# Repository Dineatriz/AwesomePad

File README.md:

# AwesomePad
---

## Overview

This macropad was made and designed to help gamers who frequently use Discord and people who do livestreams. With 6 customizable switches, a 2U switch with push-to-talk functionality, 3 configurable knobs, and an OLED panel, it can do almost anything the user wants.

---

## Schematic

---

## PCB

---

## Case

The case is 3D printed in 2 parts (Top + Bottom) and fits the PCB snugly with cutouts for all switches, the encoder, the OLED, knobs, and the USB-C port.

---

## BOM (Bill of Materials)

## Main Components
| Item           | Qtd. | Name                                                         | Link                        | Price(USD)  |
| -------------- | ---- | ------------------------------------------------------------ | --------------------------- | ----------- |
| Pro Micro      | 1    | **Pro Micro ATmega32U4 5V 16MHz USB-C 24 pin**               | https://amzn.eu/d/027iGPug  | $10.68      |
| OLED Display   | 1    | **OLED 0.96 inch SSD1306 I2C 4 pin**                         | https://amzn.eu/d/0ihcXsfb  | $9.49       |
| Rotary Encoder | 3    | **EC11 rotary encoder 20mm D shaft**                         | https://amzn.eu/d/0cy0BtVi  | $10.68      |
| Switches MX    | 7    | **Cherry MX switches pack small / Gateron switches 10 pack** | https://amzn.eu/d/0iitvTCB  | $9.25       | 

## Interface
| Item          | Qtd. | Name                                      | Link                       | Price(USD)  | 
| ------------- | ---- | ----------------------------------------- | -------------------------- | ----------- |
| Keycaps 1U    | 6    | **1U keycaps MX individual PBT**          | https://amzn.eu/d/078EwmKl | $10.68      |
| Keycap 2U     | 1    | **2U keycap MX single keycap**            | https://acesse.one/y47nhj1 | $1.09       |

## Structure
| Item         | Qtd. | Name                              | Link                        | Price(USD)  |
| ------------ | ---- | --------------------------------- | --------------------------- | ----------- |
| Screws        | 6    | **M3 6mm screws Phillips**       | https://amzn.eu/d/05gWZ59w  | $10.68      |
| Rubber feet  | 4    | **adhesive rubber feet silicone** | https://amzn.eu/d/0bTfMZw4  | $5.92       |

---

## Built by

**Dineatriz** — Hackclub 2026

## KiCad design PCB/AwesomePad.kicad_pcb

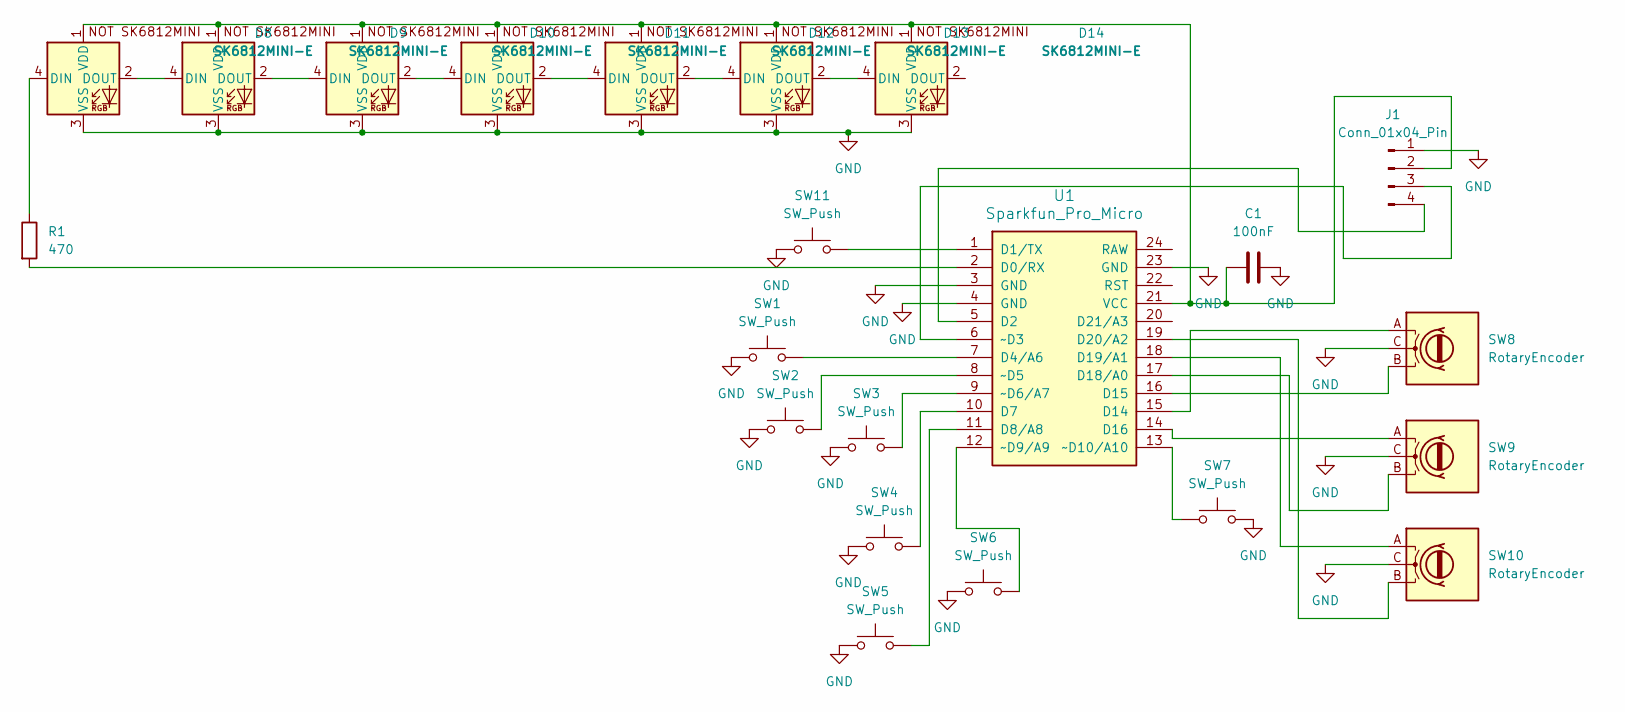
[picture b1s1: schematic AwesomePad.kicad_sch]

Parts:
C1: 100nF; C_Disc_D3.0mm_W1.6mm_P2.50mm
D8, D9, D10, D11, D12, D13, D14: SK6812MINI-E; SK6812MINI-E_fixed
J1: Conn_01x04_Pin; PinHeader_1x04_P2.54mm_Vertical
R1: 470; R_Axial_DIN0207_L6.3mm_D2.5mm_P10.16mm_Horizontal
SW1, SW2, SW3, SW4, SW5, SW6: SW_Push; SW_Cherry_MX_1.00u_PCB
SW7: SW_Push; SW_Cherry_MX_2.00u_Vertical_PCB
SW8, SW9, SW10: RotaryEncoder; RotaryEncoder_Alps_EC11E-Switch_Vertical_H20mm
SW11: SW_Push; SW_PUSH_6mm
U1: Sparkfun_Pro_Micro

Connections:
GND: C1.2, D8.3 (VSS), D9.3 (VSS), D10.3 (VSS), D11.3 (VSS), D12.3 (VSS), D13.3 (VSS), D14.3 (VSS), J1.1, SW1.1, SW2.1, SW3.1, SW4.1, SW5.1, SW6.1, SW7.2, SW8.C, SW9.C, SW10.C, SW11.1, U1.3 (GND), U1.4 (GND), U1.23 (GND)
unnamed: D8.4 (DIN), R1.1
unnamed: D8.2 (DOUT), D9.4 (DIN)
unnamed: D9.2 (DOUT), D10.4 (DIN)
unnamed: D10.2 (DOUT), D11.4 (DIN)
unnamed: C1.1, D8.1 (VDD), D9.1 (VDD), D10.1 (VDD), D11.1 (VDD), D12.1 (VDD), D13.1 (VDD), D14.1 (VDD), J1.2, U1.21 (VCC)
unnamed: D11.2 (DOUT), D12.4 (DIN)
unnamed: D12.2 (DOUT), D13.4 (DIN)
unnamed: D13.2 (DOUT), D14.4 (DIN)
unnamed: J1.3, U1.6 (~D3)
unnamed: J1.4, U1.5 (D2)
unnamed: R1.2, U1.2 (D0/RX)
unnamed: SW11.2, U1.1 (D1/TX)
unnamed: SW1.2, U1.7 (D4/A6)
unnamed: SW4.2, U1.10 (D7)
unnamed: SW5.2, U1.11 (D8/A8)
unnamed: SW8.A, U1.15 (D14)
unnamed: SW8.B, U1.16 (D15)
unnamed: SW9.A, U1.14 (D16)
unnamed: SW9.B, U1.17 (D18/A0)
unnamed: SW10.A, U1.18 (D19/A1)
unnamed: SW10.B, U1.19 (D20/A2)
unnamed: SW2.2, U1.8 (~D5)
unnamed: SW3.2, U1.9 (~D6/A7)
unnamed: SW6.2, U1.12 (~D9/A9)
unnamed: SW7.1, U1.13 (~D10/A10)

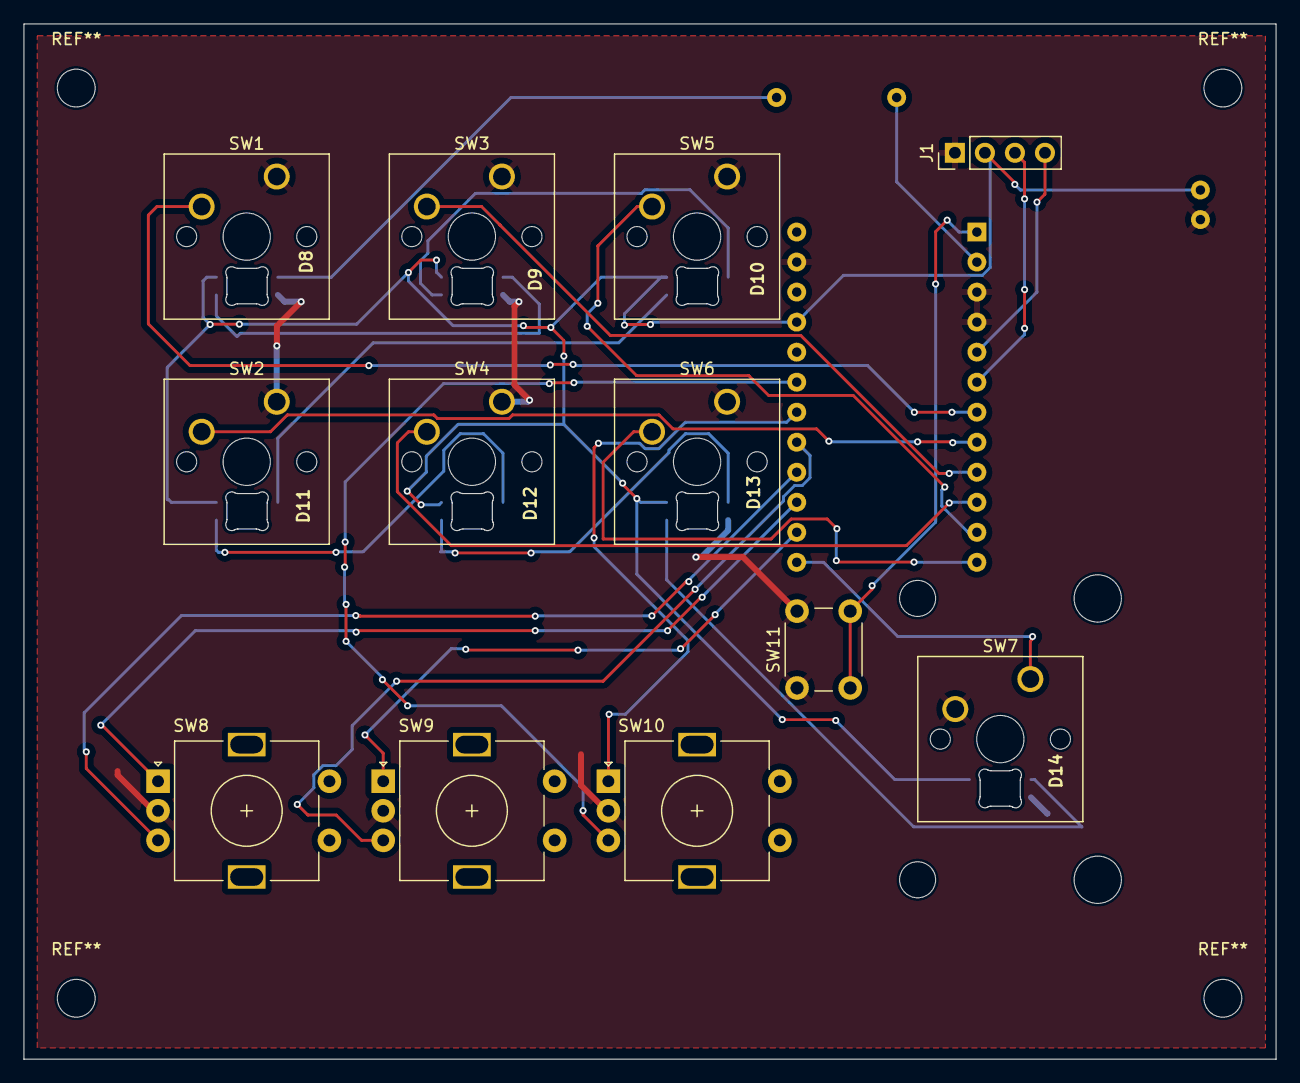
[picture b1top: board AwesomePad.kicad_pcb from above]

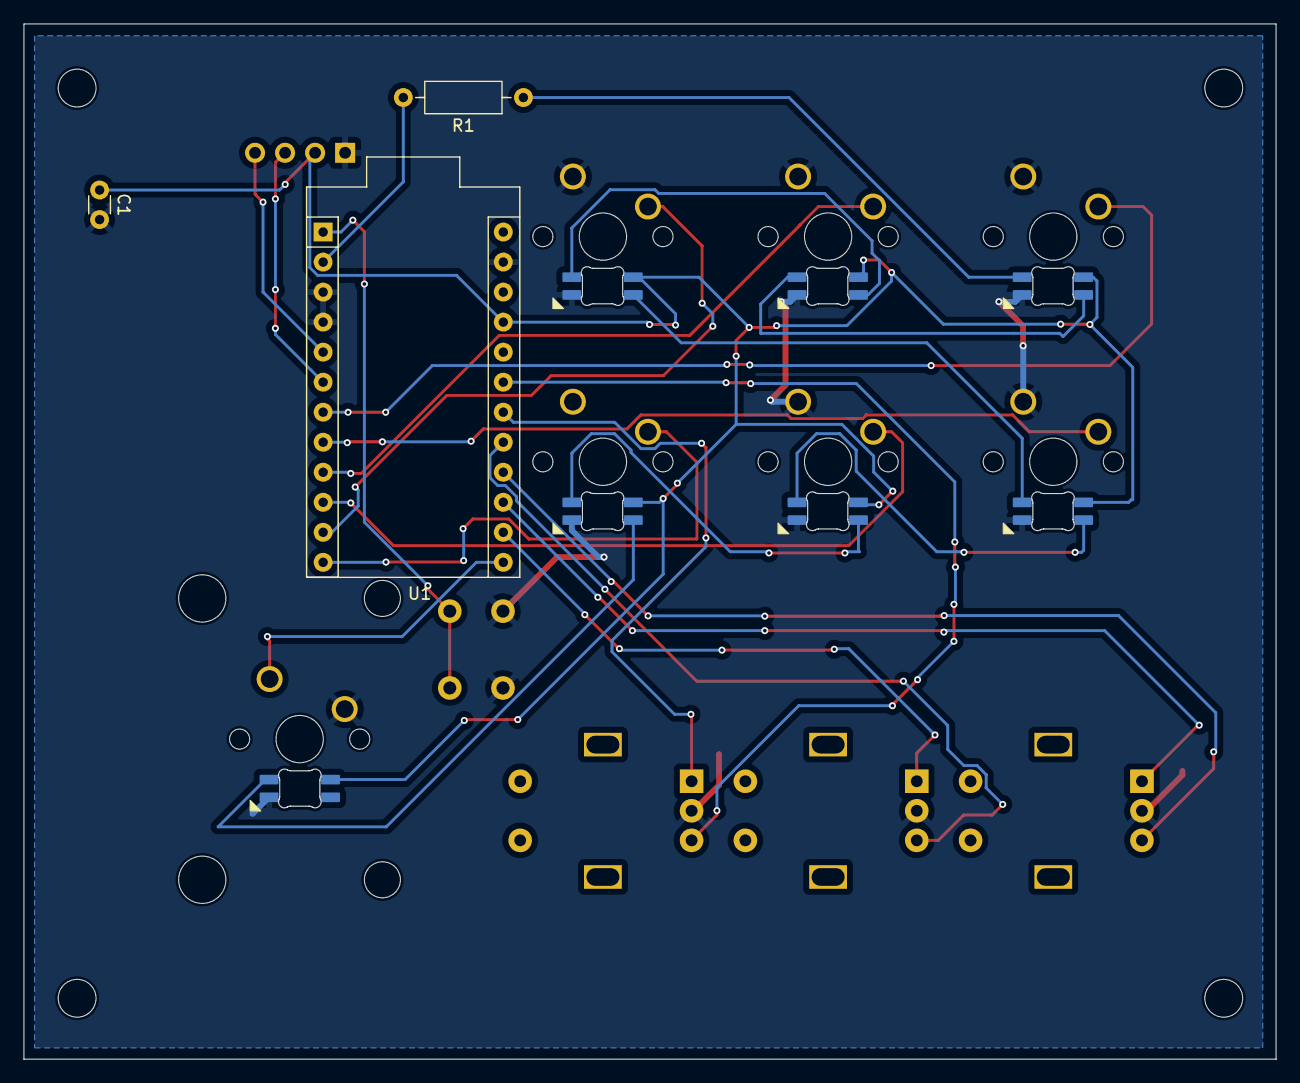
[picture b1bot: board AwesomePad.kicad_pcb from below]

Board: 2 copper layers, 105.9 x 87.5 mm, 22 parts (3 on the bottom side), 26 nets.

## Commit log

2026-04-09 Create teste
2026-04-09 Create o
2026-04-09 Add AwesomePad.kicad_pcb file
2026-04-09 Rename bu.kicad_pro to AwesomePad.kicad_pro
2026-04-09 Add AwesomePad schematic file
2026-04-09 Enhance README with detailed product information
    Expanded the README to include an overview, schematic, PCB, case details, BOM, interface, and structure sections for the AwesomePad macropad.
2026-04-09 Create a
2026-04-09 Rename Captura de ecrã 2026-04-08 163945.png to PCB_front
2026-04-09 Rename Captura de ecrã 2026-04-09 003926.png to Schematics
2026-04-09 Rename Captura de ecrã 2026-04-09 002350.png to Case
2026-04-09 Rename Captura de ecrã 2026-04-09 002343.png to Case_top
2026-04-09 Rename Captura de ecrã 2026-04-09 002323.png to Case_bottom
2026-04-09 Rename Captura de ecrã 2026-04-08 164000.png to PCB_back
2026-04-09 Rename Case to Case.png
2026-04-09 Rename Case_bottom to Case_bottom.png
2026-04-09 Rename Case_top to Case_top.png
2026-04-09 Rename PCB_back to PCB_back.png
2026-04-09 Rename PCB_front to PCB_front.png
2026-04-09 Rename Schematics to Schematics.png
2026-04-25 Add prices to BOM components in README
    Updated BOM section to include prices for components.
2026-04-25 Rename Captura de ecrã 2026-04-25 180546.png to final
2026-04-25 Change case image in README
    Updated the image in the README to the final design.
2026-04-25 Rename final to final.png
